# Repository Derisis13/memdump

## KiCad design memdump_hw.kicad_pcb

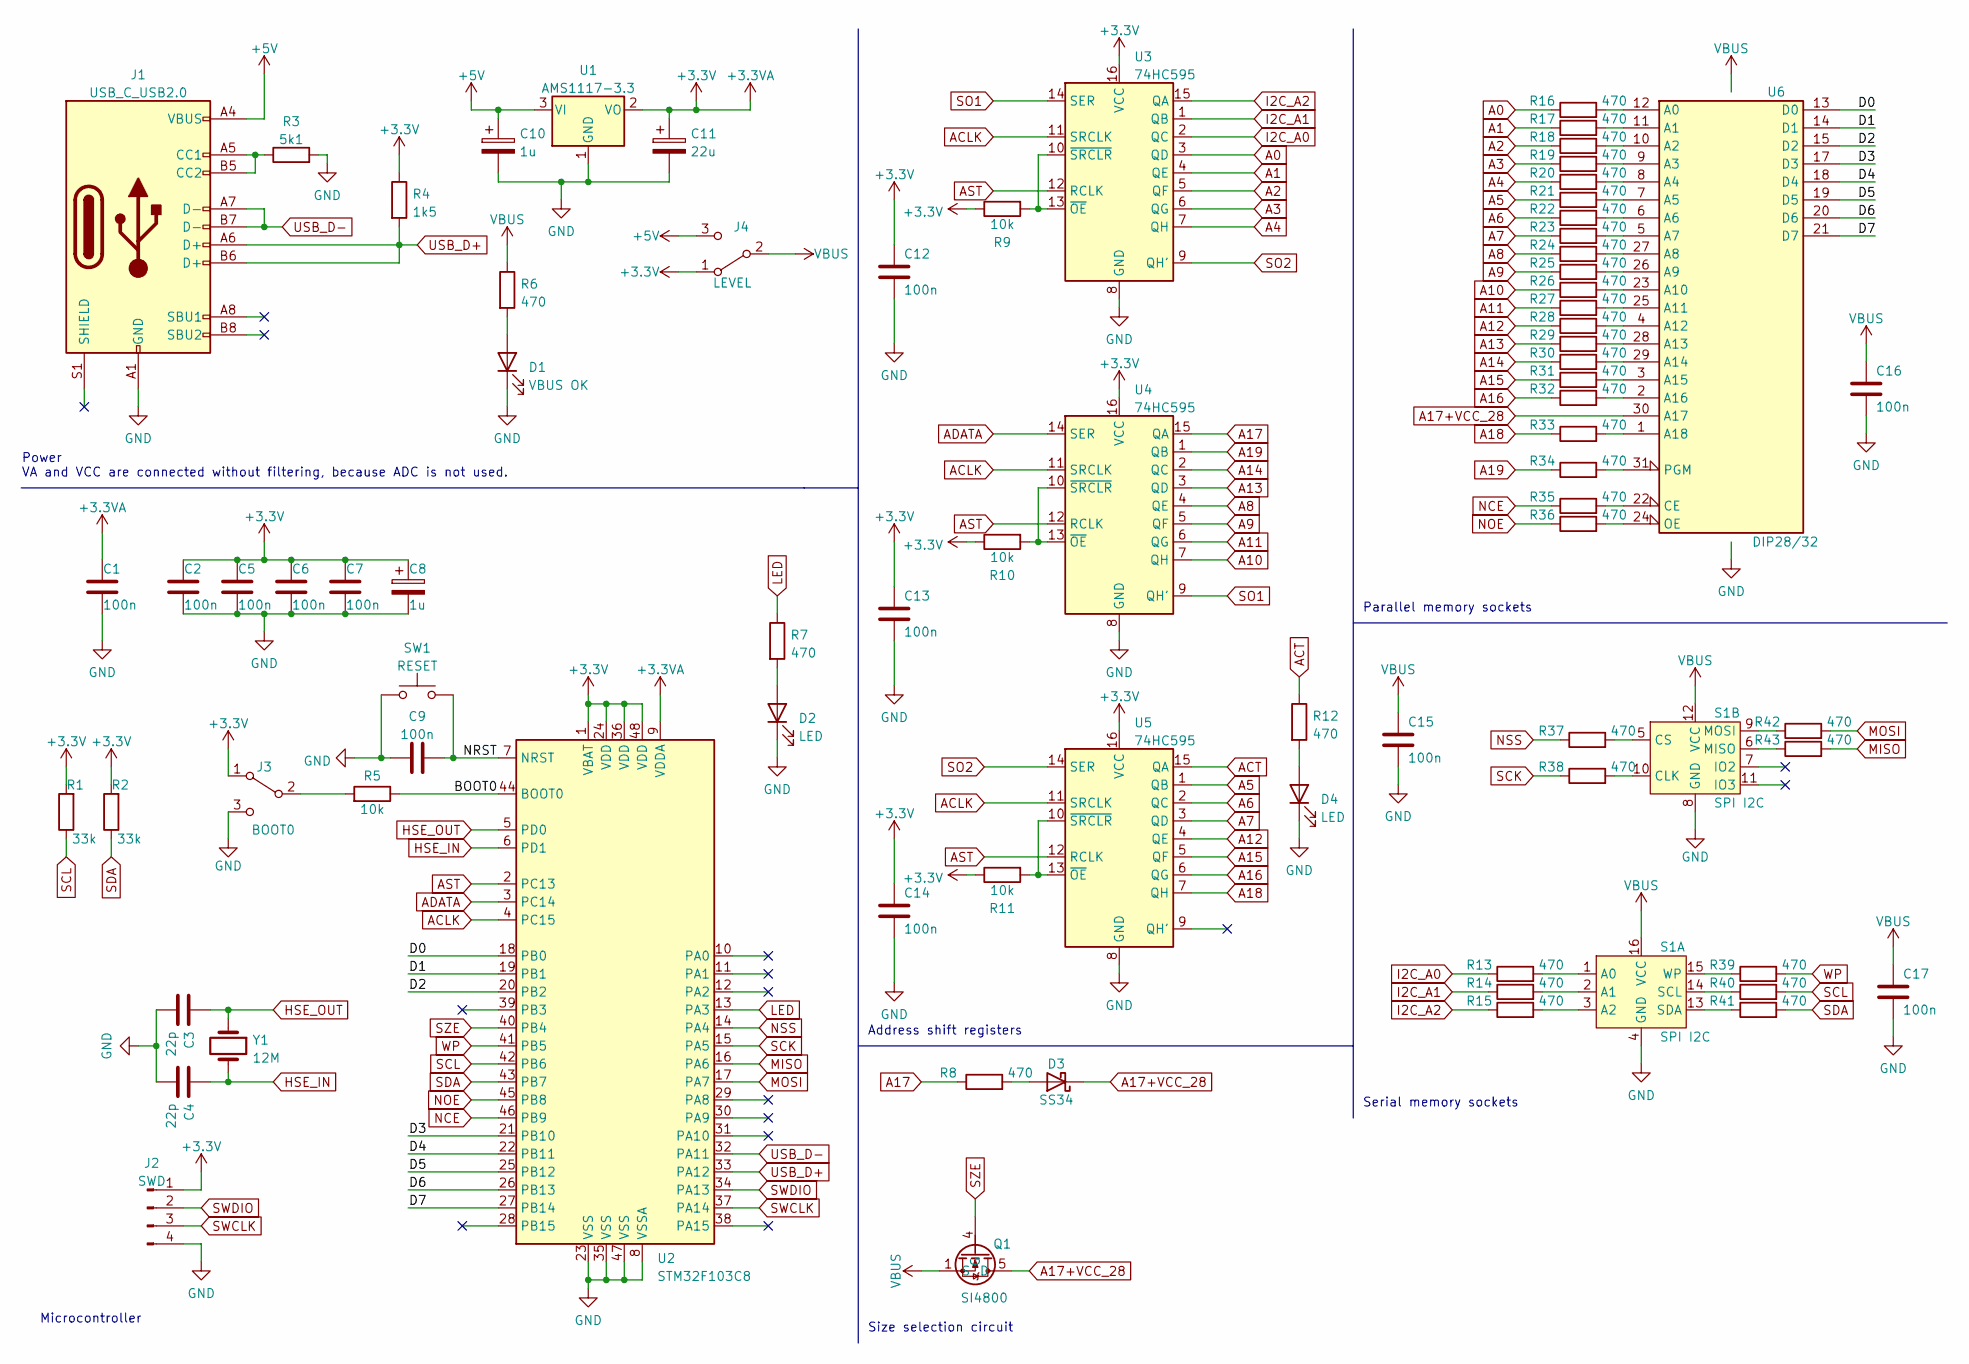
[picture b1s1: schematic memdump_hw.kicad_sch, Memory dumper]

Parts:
C1, C2, C5, C6, C7, C9, C12, C13, C14, C15, C16, C17: 100n; C_0805_2012Metric_Pad1.18x1.45mm_HandSolder
C3, C4: 22p; C_0805_2012Metric_Pad1.18x1.45mm_HandSolder
C8, C10: 1u; CP_Elec_4x4.5
C11: 22u; CP_EIA-3528-12_Kemet-T_Pad1.50x2.35mm_HandSolder
D1: VBUS OK; LED_0805_2012Metric_Pad1.15x1.40mm_HandSolder
D2, D4: LED; LED_0805_2012Metric_Pad1.15x1.40mm_HandSolder
D3: SS34; D_1206_3216Metric_Pad1.42x1.75mm_HandSolder
J1: USB_C_USB2.0; USB_C_Receptacle_HRO_TYPE-C-31-M-12
J2: SWD; PinHeader_1x04_P2.54mm_Vertical
J3: BOOT0; PinHeader_1x03_P2.54mm_Vertical
J4: LEVEL; PinHeader_1x03_P2.54mm_Vertical
Q1: SI4800; SO-8_3.9x4.9mm_P1.27mm
R1, R2: 33k; R_0805_2012Metric_Pad1.20x1.40mm_HandSolder
R3: 5k1; R_0805_2012Metric_Pad1.20x1.40mm_HandSolder
R4: 1k5; R_0805_2012Metric_Pad1.20x1.40mm_HandSolder
R5, R9, R10, R11: 10k; R_0805_2012Metric_Pad1.20x1.40mm_HandSolder
R6, R7, R8, R12, R13, R14, R15, R16, R17, R18, R19, R20, R21, R22, R23, R24, R25, R26, R27, R28, R29, R30, R31, R32, R33, R34, R35, R36, R37, R38, R39, R40, R41, R42, R43: 470; R_0805_2012Metric_Pad1.20x1.40mm_HandSolder
S1: SPI I2C; DIP_Socket-16_W4.3_W5.08_W7.62_W10.16_W10.9_3M_216-3340-00-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
SW1: RESET; SW_Push_SPST_NO_Alps_SKRK
U1: AMS1117-3.3; SOT-223-3_TabPin2
U2: STM32F103C8; LQFP-48_7x7mm_P0.5mm
U3, U4, U5: 74HC595; SOP-16_3.9x9.9mm_P1.27mm
U6: DIP28/32; DIP_Socket-32_W11.9_W12.7_W15.24_W17.78_W18.5_3M_232-1285-0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
Y1: 12M; Crystal_HC18-U_Vertical

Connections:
+3.3VA: C1.1, C2.1, C5.1, C6.1, C7.1, C8.1, C11.1, C12.1, C13.1, C14.1, J2.1, J3.1 (A), J4.1 (A), R1.2, R2.2, R4.1, R9.1, R10.1, R11.1, U1.2 (VO), U2.1 (VBAT), U2.9 (VDDA), U2.24 (VDD), U2.36 (VDD), U2.48 (VDD), U3.16 (VCC), U4.16 (VCC), U5.16 (VCC)
+5V: C10.1, J1.A4 (VBUS), J1.A9 (VBUS), J1.B4 (VBUS), J1.B9 (VBUS), J4.3 (C), U1.3 (VI)
/BOOT0: R5.1, U2.44 (BOOT0)
/D0: U2.18 (PB0), U6.13 (D0)
/D1: U2.19 (PB1), U6.14 (D1)
/D2: U2.20 (PB2), U6.15 (D2)
/D3: U2.21 (PB10), U6.17 (D3)
/D4: U2.22 (PB11), U6.18 (D4)
/D5: U2.25 (PB12), U6.19 (D5)
/D6: U2.26 (PB13), U6.20 (D6)
/D7: U2.27 (PB14), U6.21 (D7)
/NRST: C9.2, SW1.2, U2.7 (NRST)
A0: R16.1, U3.3 (QD)
A1: R17.1, U3.4 (QE)
A2: R18.1, U3.5 (QF)
A3: R19.1, U3.6 (QG)
A4: R20.1, U3.7 (QH)
A5: R21.1, U5.1 (QB)
A6: R22.1, U5.2 (QC)
A7: R23.1, U5.3 (QD)
A8: R24.1, U4.4 (QE)
A9: R25.1, U4.5 (QF)
A10: R26.1, U4.7 (QH)
A11: R27.1, U4.6 (QG)
A12: R28.1, U5.4 (QE)
A13: R29.1, U4.3 (QD)
A14: R30.1, U4.2 (QC)
A15: R31.1, U5.5 (QF)
A16: R32.1, U5.6 (QG)
A17: R8.1, U4.15 (QA)
A17+VCC_28: D3.1 (K), Q1.5 (D), Q1.6 (D), Q1.7 (D), Q1.8 (D), U6.30 (A17)
A18: R33.1, U5.7 (QH)
A19: R34.1, U4.1 (QB)
ACLK: U2.4 (PC15), U3.11 (SRCLK), U4.11 (SRCLK), U5.11 (SRCLK)
ACT: R12.1, U5.15 (QA)
ADATA: U2.3 (PC14), U4.14 (SER)
AST: U2.2 (PC13), U3.12 (RCLK), U4.12 (RCLK), U5.12 (RCLK)
GND: C1.2, C2.2, C3.2, C4.1, C5.2, C6.2, C7.2, C8.2, C9.1, C10.2, C11.2, C12.2, C13.2, C14.2, C15.2, C16.2, C17.2, D1.1 (K), D2.1 (K), D4.1 (K), J1.A1 (GND), J1.A12 (GND), J1.B1 (GND), J1.B12 (GND), J2.4, J3.3 (C), R3.2, S1.4 (GND), S1.8 (GND), SW1.1, U1.1 (GND), U2.8 (VSSA), U2.23 (VSS), U2.35 (VSS), U2.47 (VSS), U3.8 (GND), U4.8 (GND), U5.8 (GND), U6.16 (GND)
HSE_IN: C4.2, U2.6 (PD1), Y1.2
HSE_OUT: C3.1, U2.5 (PD0), Y1.1
I2C_A0: R13.1, U3.2 (QC)
I2C_A1: R14.1, U3.1 (QB)
I2C_A2: R15.1, U3.15 (QA)
LED: R7.1, U2.13 (PA3)
MISO: R43.2, U2.16 (PA6)
MOSI: R42.2, U2.17 (PA7)
NCE: R35.1, U2.46 (PB9)
NOE: R36.1, U2.45 (PB8)
NSS: R37.1, U2.14 (PA4)
unnamed: D1.2 (A), R6.2
unnamed: D2.2 (A), R7.2
unnamed: D3.2 (A), R8.2
unnamed: D4.2 (A), R12.2
unnamed: J3.2 (B), R5.2
unnamed: J1.A5 (CC1), J1.B5 (CC2), R3.1
unnamed: R9.2, U3.10 (~SRCLR), U3.13 (~OE)
unnamed: R10.2, U4.10 (~SRCLR), U4.13 (~OE)
unnamed: R11.2, U5.10 (~SRCLR), U5.13 (~OE)
unnamed: R13.2, S1.1 (A0)
unnamed: R14.2, S1.2 (A1)
unnamed: R15.2, S1.3 (A2)
unnamed: R16.2, U6.12 (A0)
unnamed: R17.2, U6.11 (A1)
unnamed: R18.2, U6.10 (A2)
unnamed: R19.2, U6.9 (A3)
unnamed: R20.2, U6.8 (A4)
unnamed: R21.2, U6.7 (A5)
unnamed: R22.2, U6.6 (A6)
unnamed: R23.2, U6.5 (A7)
unnamed: R24.2, U6.27 (A8)
unnamed: R25.2, U6.26 (A9)
unnamed: R26.2, U6.23 (A10)
unnamed: R27.2, U6.25 (A11)
unnamed: R28.2, U6.4 (A12)
unnamed: R29.2, U6.28 (A13)
unnamed: R30.2, U6.29 (A14)
unnamed: R31.2, U6.3 (A15)
unnamed: R32.2, U6.2 (A16)
unnamed: R33.2, U6.1 (A18)
unnamed: R34.2, U6.31 (PGM)
unnamed: R35.2, U6.22 (CE)
unnamed: R36.2, U6.24 (OE)
unnamed: R37.2, S1.5 (CS)
unnamed: R38.2, S1.10 (CLK)
unnamed: R39.1, S1.15 (WP)
unnamed: R40.1, S1.14 (SCL)
unnamed: R41.1, S1.13 (SDA)
unnamed: R42.1, S1.9 (MOSI)
unnamed: R43.1, S1.6 (MISO)
SCK: R38.1, U2.15 (PA5)
SCL: R1.1, R40.2, U2.42 (PB6)
SDA: R2.1, R41.2, U2.43 (PB7)
SO1: U3.14 (SER), U4.9 (QH')
SO2: U3.9 (QH'), U5.14 (SER)
SWCLK: J2.3, U2.37 (PA14)
SWDIO: J2.2, U2.34 (PA13)
SZE: Q1.4 (G), U2.40 (PB4)
USB_D+: J1.A6 (D+), J1.B6 (D+), R4.2, U2.33 (PA12)
USB_D-: J1.A7 (D-), J1.B7 (D-), U2.32 (PA11)
VBUS: C15.1, C16.1, C17.1, J4.2 (B), Q1.1 (S), Q1.2 (S), Q1.3 (S), R6.1, S1.12 (VCC), S1.16 (VCC), U6.32 (VCC)
WP: R39.2, U2.41 (PB5)

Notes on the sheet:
Address shift registers
Size selection circuit
Power VA and VCC are connected without filtering, because ADC is not used.
Microcontroller
Serial memory sockets
Parallel memory sockets

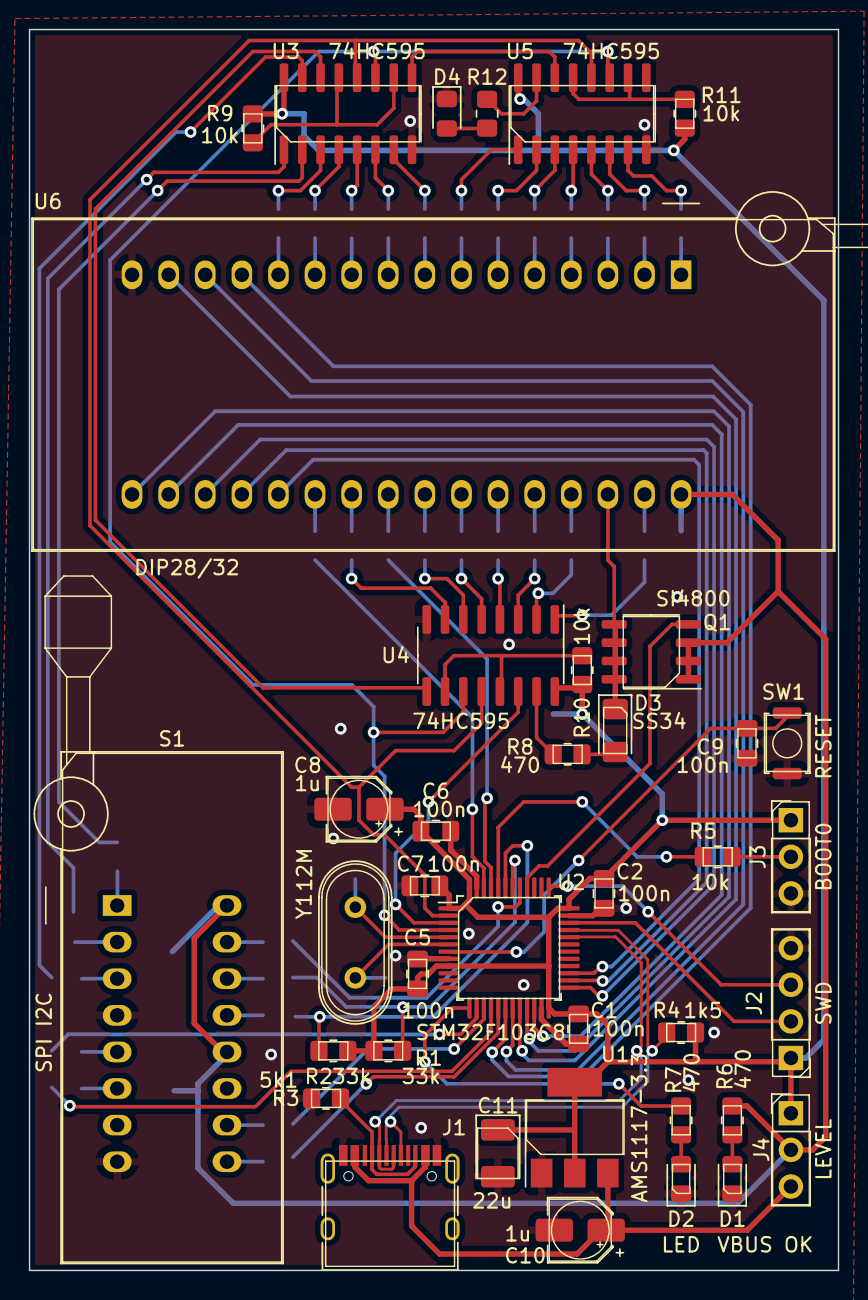
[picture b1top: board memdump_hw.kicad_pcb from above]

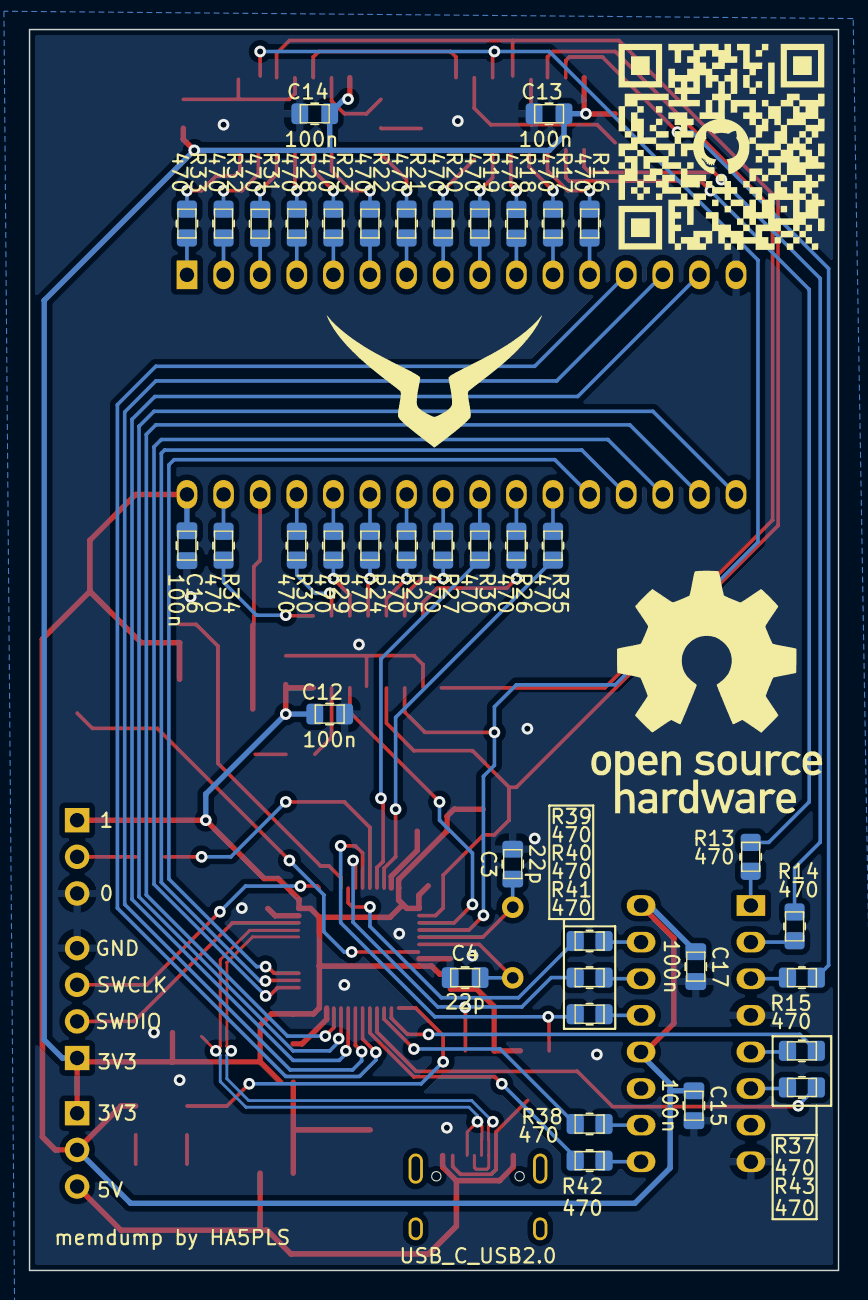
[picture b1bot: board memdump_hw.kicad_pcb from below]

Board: 2 copper layers, 56.1 x 86.1 mm, 78 parts (39 on the bottom side), 101 nets.

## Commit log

2022-10-15 Innitial commit, rev. 0.1 Schematic only
2022-10-17 *feat: current limiting resistors for protection on all memory pins *feat: begin footprint assignment *feat: I2C address manipulation via the end of the shift register line
2022-10-26 chore: updated gitignore fix: changed to 4094 fix: better layout
2022-10-26 fix: change to 74HC595 fix: all tracks are routed fix: GND is now continuous fix: everything else, the board is pretty much complete
2022-10-27 fix: changed protection resistances to 470R for faster operation
2022-10-27 fix: moved R22 to the shiftreg side of the size selection circuit
2022-10-27 fix: pcb implementation of schematic changes fix: less sharp corners feat: more ground infill with GND vias
2022-10-28 feat: PCB prints update: actualized schematic pdf
2022-10-28 fix: minor cleanup fix: branching from vias when possible fix: values moved to the respective silkscreens
2022-10-28 feat: pcb render screenshots fix: labels
2022-12-10 fix: USB-C to UFP
2024-07-30 docs: pcb pictures
